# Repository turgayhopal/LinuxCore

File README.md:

# Linux-Core Development Board

- This project goal is developing myself about embedded linux environment like buildroot, the yacto project.

### Linux Core v2 Features

- NUC980 Series Microprocessor
- 2A Step-Down Voltage Regulator 1.2V, 1.8V, 3.3V
- RLT8188EU WIFI USB Module
- CP2102 USB TTL
- ILI9143 TFT LCD Header
- NAU88C22YG Audio Speaker
- Cam Slot
- SPI Nand External Flash
- MDBT5DQ (NRF52840 Bluetooth Bodule with USB) (Experimental !!!)
- 2 USB Host Socket
- 2 - 2x10 User Pin Header
- SD Card Slot
- 4 User LED's

### PCB Features

- 60.1mm x 80.1mm
- 1mm board thickness.
- 4 layer PCB.
- 0.45 / 0.3 vias

### Linux Core v1 Features

- NUC980 Series Microprocessor
- 2A Step-Down Voltage Regulator 1.2V, 1.8V, 3.3V
- RLT8188EU WIFI USB Module
- CP2102 USB TTL
- 128 KB External SPI-NOR Flash
- SD Card Slot
- 3 User LED's

### PCB Features

- 52.6mm x 57.5mm
- 1.6mm board thickness.
- 2 layer PCB.
- 0.6 / 0.3 vias

## Linux Core v2 Images

### Right Side

### Front Side

### Back Side

### LCD

## Linux Core v1 Images

### Right Side

### Front Side

### Back Side

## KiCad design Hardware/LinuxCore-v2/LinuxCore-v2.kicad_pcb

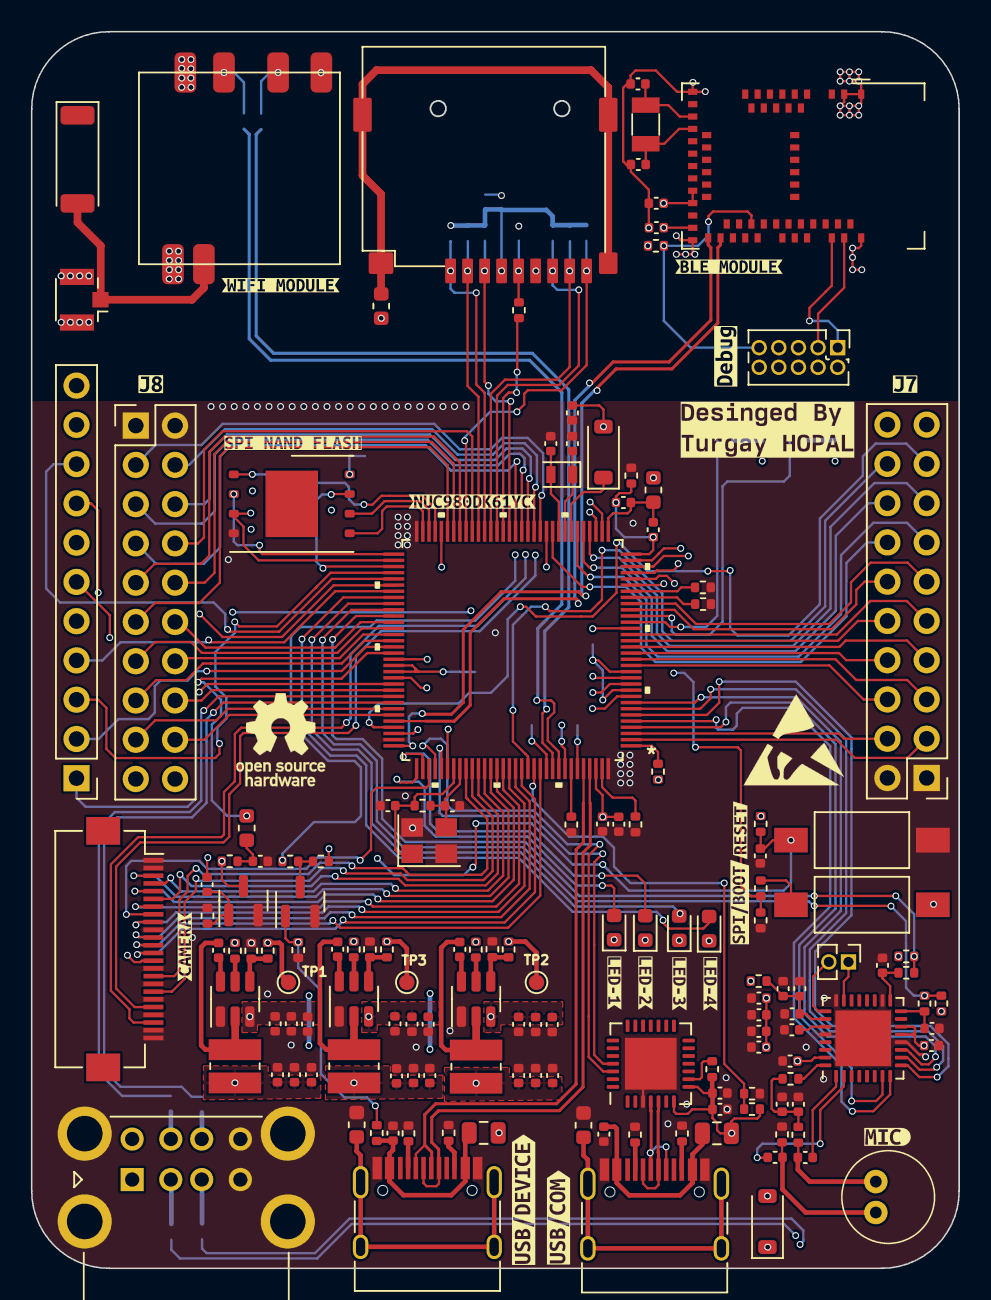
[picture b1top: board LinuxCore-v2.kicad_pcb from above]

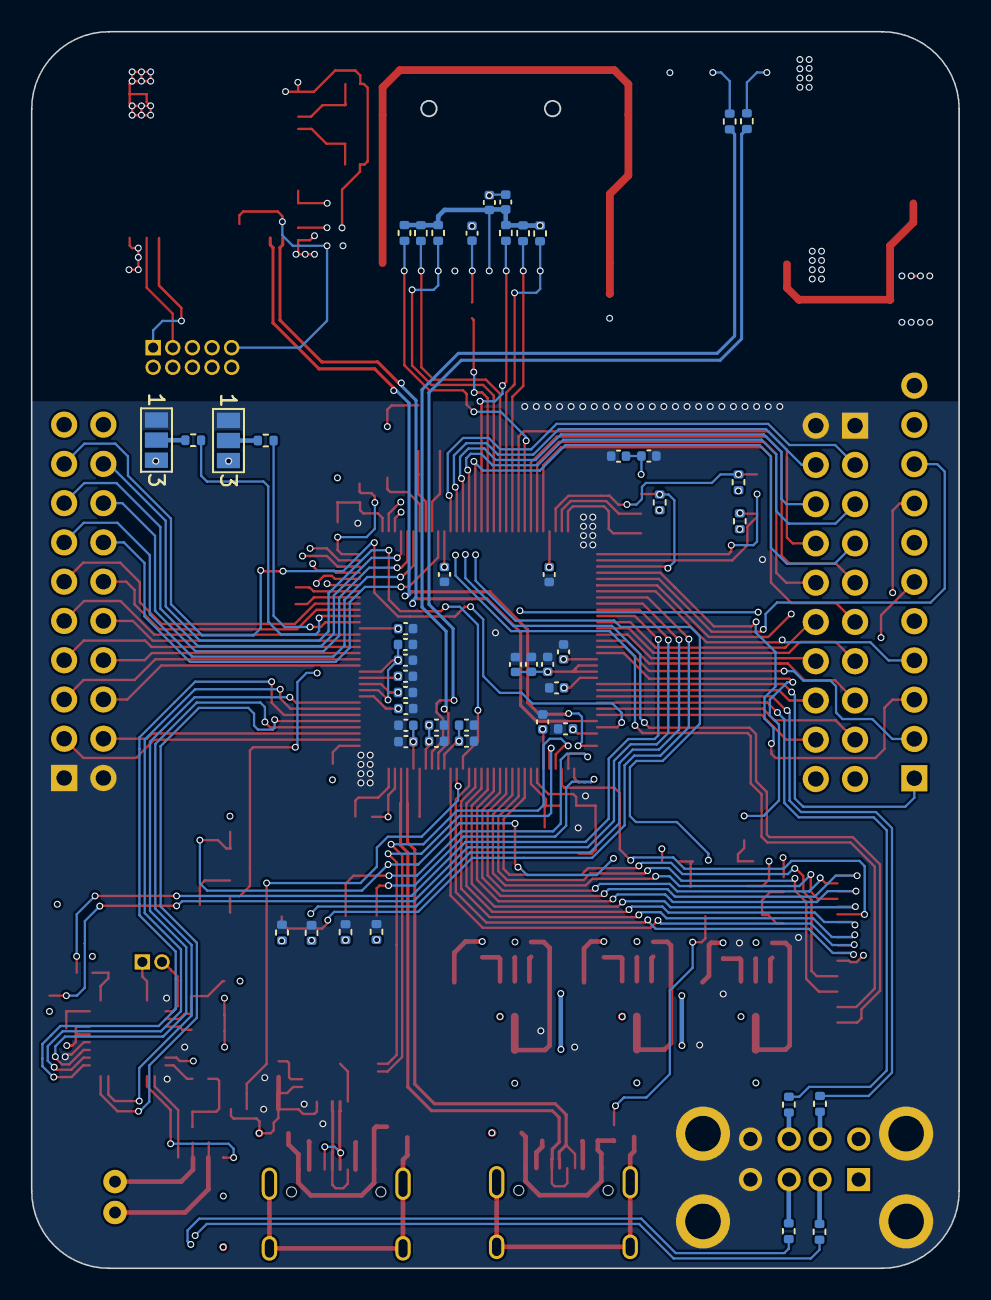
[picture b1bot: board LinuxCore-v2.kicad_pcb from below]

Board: 4 copper layers, 60.0 x 80.0 mm, 214 parts (49 on the bottom side), 174 nets.

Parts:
AE1: Antenna_Shield; U.FL_Hirose_U.FL-R-SMT-1_Vertical
AE2: Antenna_Shield; Johanson_2450AT43F0100
C1, C2, C3, C8: 15pF; C_0402_1005Metric
C4, C5, C6, C12, C33, C34, C38, C39, C40, C41, C42, C43, C61, C65, C66, C67, C69, C72, C78: 10uF; C_0402_1005Metric
C7, C9, C10, C11, C13, C17, C18, C19, C20, C21, C22, C23, C24, C25, C26, C27, C29, C30, C31, C32, C36, C37, C44, C45, C46, C47, C48, C49, C50, C51, C52, C60: 0.1uF; C_0402_1005Metric
C14, C15, C16, C28, C35, C53, C54, C55, C56, C57, C58, C70, C71: 1uF; C_0402_1005Metric
C59: NC; C_0402_1005Metric
C62, C63, C64, C68, C73, C74, C75, C77, C79: 100nF; C_0402_1005Metric
C76, C82, C83: 4.7uF; C_0402_1005Metric
C80, C81: 12pF; C_0402_1005Metric
D1: 30V 200mA; D_SOD-123
D2: B240; D_SOD-123
D3, D4, D5, D6: LED; LED_0603_1608Metric
F1, F2: 6V/1.5A; Fuse_0805_2012Metric
J1, J2: USB_C_Receptacle_USB2.0; USB_C_Receptacle_HRO_TYPE-C-31-M-12
J3: Conn_01x11_Pin; PinHeader_1x11_P2.54mm_Vertical
J4: Conn_01x24; Hirose_FH12-24S-0.5SH_1x24-1MP_P0.50mm_Horizontal
J5: NRF_Debug; PinHeader_2x05_P1.27mm_Vertical
J6: USB_A_Stacked; USB_A_CUI_UJ2-ADH-TH_Horizontal_Stacked
J7, J8: Conn_02x10_Odd_Even; PinHeader_2x10_P2.54mm_Vertical
JP1, JP2: SolderJumper_3_Open; SolderJumper-3_P1.3mm_Open_Pad1.0x1.5mm_NumberLabels
L1, L2, L3, L4, L8: 220R; L_0603_1608Metric
L5, L6, L7: 2.2uH; L_Wuerth_MAPI-3020
LS1: Speaker; PinHeader_1x02_P1.27mm_Vertical
Q1, Q2: MMBT3904; SOT-23
R1: 1M; R_0402_1005Metric
R2, R37, R48: 0R; R_0402_1005Metric
R3, R4, R12: 100K; R_0402_1005Metric
R5: 470R; R_0402_1005Metric
R6, R21, R23, R60, R61, R62, R63: 1K; R_0402_1005Metric
R7, R8, R25, R26, R56, R57, R58, R59: 5.1K; R_0402_1005Metric
R9: 20K; R_0402_1005Metric
R10: 39K; R_0402_1005Metric
R11, R13: 12.1K; R_0402_1005Metric
R14, R15: 4.7R; R_0402_1005Metric
R16, R17, R18, R19, R20, R22, R24, R27, R28, R29, R30, R31, R32, R33, R38, R39, R40, R41, R42, R43, R52, R53, R54, R55: 10K; R_0402_1005Metric
R34: 33.2K; R_0402_1005Metric
R35: 5.76K; R_0402_1005Metric
R36: 13.7K; R_0402_1005Metric
R44, R45, R46, R47: 33R; R_0402_1005Metric
R49, R50: 2.2K; R_0402_1005Metric
R51: 680R; R_0402_1005Metric
SW1, SW2: SW_Push; SW_SPST_FSMSM
TP1, TP2, TP3: TestPoint; TestPoint_Pad_D1.0mm
U1: NUC980DK61YC
U2: RLT8188_WIFI_MODUL
U3: CP2102N-Axx-xQFN28; QFN-28-1EP_5x5mm_P0.5mm_EP3.35x3.35mm
U4, U5, U6: TPS562200; SOT-23-6
U7: L-KLS1-TF-003; L-KLS1-TF-003-H1.85-R
U8: NAU88C22; QFN-32-1EP_5x5mm_P0.5mm_EP3.6x3.6mm
U9: F35SQA001G
U10: MDBT50Q-P1MV2; Raytac_MDBT50Q
U11: L-KLS3-MM6027PP-443
Y1: Crystal; Crystal_SMD_2012-2Pin_2.0x1.2mm
Y2: Crystal_GND24; Crystal_SMD_3225-4Pin_3.2x2.5mm
Y3: 32.768kHz; Crystal_SMD_3215-2Pin_3.2x1.5mm
kibuzzard-665B7D91: G***; kibuzzard-665B7D91
kibuzzard-665B7DAC: G***; kibuzzard-665B7DAC
kibuzzard-665B7DDA: G***; kibuzzard-665B7DDA
kibuzzard-665B7E6F: G***; kibuzzard-665B7E6F
kibuzzard-665B7E8B: G***; kibuzzard-665B7E8B
kibuzzard-665B7E24: G***; kibuzzard-665B7E24
kibuzzard-665B7E38: G***; kibuzzard-665B7E38
kibuzzard-665B7E84: G***; kibuzzard-665B7E84
kibuzzard-665B7E87: G***; kibuzzard-665B7E87
kibuzzard-665B7EA2: G***; kibuzzard-665B7EA2
kibuzzard-665B7EF0: G***; kibuzzard-665B7EF0
kibuzzard-665B7F01: G***; kibuzzard-665B7F01
kibuzzard-665B7F18: G***; kibuzzard-665B7F18
kibuzzard-665B7F32: G***; kibuzzard-665B7F32
kibuzzard-665B7FB9: G***; kibuzzard-665B7FB9
kibuzzard-665B7FBD: G***; kibuzzard-665B7FBD
kibuzzard-665C90BB: G***; kibuzzard-665C90BB
kibuzzard-665C92C9: G***; kibuzzard-665C92C9

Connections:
+1V2: C6.2, C11.2, C14.1, C17.2, C19.2, C22.2, C25.2, C29.2, C32.2, C34.2, C52.2, C55.2, C58.2, L7.2, R35.2, TP2.1, U1.10 (VDD), U1.13 (VDD), U1.43 (VDD), U1.82 (VDD), U1.94 (VDD), U1.118 (VDD), U1.123 (USB0_VDD)
+1V8: C20.1, C23.1, C26.1, C30.1, C33.1, C51.2, C54.2, C57.2, L6.2, R36.2, TP3.1, U1.11 (MVDD), U1.12 (MVDD), U1.83 (MVDD), U1.84 (MVDD)
+3V3: C4.2, C5.2, C7.2, C9.2, C10.2, C18.1, C21.1, C24.1, C27.1, C31.1, C50.2, C53.2, C56.2, C60.1, C61.1, C62.1, C63.1, C64.1, C66.1, C74.1, C75.2, C78.2, C79.2, C83.2, D1.2 (A), J3.5, J3.7, J3.10, J4.14, J5.2, J7.19, J7.20, J8.19, J8.20, JP1.3 (B), JP2.3 (B), L1.1, L5.2, R4.1, R12.1, R19.1, R34.2, R38.2, R39.2, R40.2, R41.2, R42.2, R43.2, R44.2, R45.2, R48.1, R52.1, R53.2, R54.1, R55.2, SW2.1, TP1.1, U1.9 (VDDIO), U1.20 (VDDIO), U1.60 (VDDIO), U1.85 (VDDIO), U1.102 (VDDIO), U1.121 (USB1_VDD33), U1.126 (USB0_VDD33), U2.1 (3V3), U7.4 (VDD), U8.13 (VDDC), U8.14 (VDDB), U8.31 (VDDA), U9.8 (VCC), U10.28 (VDD), U10.30 (VDDH)
/AUDIO/I2S_BCLK: U1.5 (PA-3), U8.8 (BCLK)
/AUDIO/I2S_DI: U1.6 (PA-4), U8.9 (ADCOUT)
/AUDIO/I2S_DO: U1.7 (PA-5), U8.10 (DACIN)
/AUDIO/I2S_LRCK: U1.4 (PA-2), U8.7 (FS)
/AUDIO/I2S_MCLK: U1.8 (PA-6), U8.11 (MCLK)
/AUDIO/LMICN: C71.2, U8.2 (LMICN)
/AUDIO/LMICP: C70.2, U8.1 (LMICP)
/AUDIO/LSPKOUT: LS1.2, U8.25 (LSPKOUT)
/AUDIO/RSPKOUT: LS1.1, U8.23 (RSPKOUT)
/AUDIO/SCL: R45.1, R47.1, U1.74 (PD-14)
/AUDIO/SCL_: C67.1, R47.2, U8.16 (SCLK)
/AUDIO/SDA: R44.1, R46.1, U1.75 (PD-15)
/AUDIO/SDA_: C65.1, R46.2, U8.17 (SDIO)
/AUDIO/SPK_3V3: C68.1, C69.1, C77.2, R48.2, U8.26 (VDDSPK)
/AUDIO/VREF: C76.2, U8.27 (VREF)
/BLE Module/NRESET: J5.9, R55.1, U10.40 (~RESET/P0.18)
/BLE Module/SWDCLK: J5.3, U10.53 (SWDCLK)
/BLE Module/SWDIO: J5.1, U10.51 (SWDIO)
/BLE Module/USB_D+: U1.96 (PF-7), U10.35 (D+)
/BLE Module/USB_D-: U1.92 (PF-6), U10.34 (D-)
/BLE Module/XL1: C80.1, U10.17 (XL1/P0.00), Y3.1
/BLE Module/XL2: C81.1, U10.18 (XL2/P0.01), Y3.2
/Deneyap Kamera/CAMD2: J4.6, U1.107 (PE-2)
/Deneyap Kamera/CAMD3: J4.4, U1.108 (PE-3)
/Deneyap Kamera/CAMD4: J4.3, U1.109 (PE-4)
/Deneyap Kamera/CAMD5: J4.5, U1.110 (PE-5)
/Deneyap Kamera/CAMD6: J4.7, U1.111 (PE-6)
/Deneyap Kamera/CAMD7: J4.9, U1.112 (PE-7)
/Deneyap Kamera/CAMD8: J4.11, U1.113 (PE-8)
/Deneyap Kamera/CAMD9: J4.13, U1.114 (PE-9)
/Deneyap Kamera/CAMH: J4.16, U1.105 (PE-0)
/Deneyap Kamera/CAMPC: J4.8, U1.99 (PF-10)
/Deneyap Kamera/CAMSC: J4.20, U1.35 (PB-5)
/Deneyap Kamera/CAMSD: J4.22, U1.34 (PB-7)
/Deneyap Kamera/CAMV: J4.18, U1.106 (PE-1)
/Deneyap Kamera/CAMXC: J4.12, U1.117 (PE-12)
/Header1/3: J7.3, U1.2 (PA-0)
/Header1/4: J7.4, U1.3 (PA-1)
/Header1/5: J7.5, U1.15 (PA-8)
/Header1/6: J7.6, U1.14 (PA-7)
/Header1/7: J7.7, U1.17 (PA-10)
/Header1/8: J7.8, U1.16 (PA-9)
/Header1/9: J7.9, U1.19 (PA-12)
/Header1/10: J7.10, U1.18 (PA-11)
/Header1/11: J7.11, U1.24 (PG-6)
/Header1/12: J7.12, U1.23 (PG-7)
/Header1/13: J7.13, U1.38 (PB-2)
/Header1/14: J7.14, U1.42 (PB-8)
/Header1/15: J7.15, U1.36 (PB-1)
/Header1/16: J7.16, U1.37 (PB-3)
/Header1/17: J7.17, U1.93 (PB-13)
/Header1/18: J7.18, U1.115 (PE-10)
/Header2/3: J8.3, U1.44 (PC-0)
/Header2/4: J8.4, U1.45 (PC-1)
/Header2/5: J8.5, U1.47 (PC-3)
/Header2/6: J8.6, U1.46 (PC-2)
/Header2/7: J8.7, U1.48 (PC-4)
/Header2/8: J8.8, U1.55 (PC-11)
/Header2/9: J8.9, U1.57 (PC-13)
/Header2/10: J8.10, U1.58 (PC-14)
/Header2/11: J8.11, U1.59 (PC-15)
/Header2/12: J8.12, U1.76 (PG-11)
/Header2/13: J8.13, U1.77 (PG-12)
/Header2/14: J8.14, U1.78 (PG-13)
/Header2/15: J8.15, U1.79 (PG-14)
/Header2/16: J8.16, U1.87 (PF-1)
/Header2/17: J8.17, U1.90 (PF-4)
/Header2/18: J8.18, U1.91 (PF-5)
/ILI9143 TFT LCD/CLK: J3.9, U1.69 (PD-9)
/ILI9143 TFT LCD/CS1: J3.3, U1.68 (PD-8)
/ILI9143 TFT LCD/CS2: J3.2, U1.80 (PG-15)
/ILI9143 TFT LCD/DC: J3.6, U1.29 (PB-0)
/ILI9143 TFT LCD/MISO: J3.4, U1.71 (PD-11)
/ILI9143 TFT LCD/MOSI: J3.8, U1.70 (PD-10)
/ILI9143 TFT LCD/PEN: J3.1, U1.86 (PF-0)
/MPU/PB4: R56.2, U1.31 (PB-4)
/MPU/PB6: R57.2, U1.30 (PB-6)
/MPU/PC5: R42.1, U1.49 (PC-5), U7.3 (CMD)
/MPU/PC6: R37.2, U1.50 (PC-6)
/MPU/PC7: R43.1, U1.51 (PC-7), U7.7 (DAT0)
/MPU/PC8: R41.1, U1.52 (PC-8), U7.8 (DAT1)
/MPU/PC9: R38.1, U1.53 (PC-9), U7.1 (DAT2)
/MPU/PC10: R40.1, U1.54 (PC-10), U7.2 (CD/DAT3)
/MPU/PC12: R39.1, U1.56 (PC-12), U7.9 (CD)
/MPU/PD2: R53.1, U1.61 (PD-2), U9.1 (CS#)
/MPU/PD3: U1.62 (PD-3), U9.6 (CLK)
/MPU/PD4: U1.63 (PD-4), U9.5 (DI/SIO0)
/MPU/PD5: U1.65 (PD-5), U9.2 (DO/SIO1)
/MPU/PD6: R52.2, U1.66 (PD-6), U9.3 (WP#/SIO2)
/MPU/PD7: R54.2, U1.67 (PD-7), U9.7 (HOLD#/SIO3)
/MPU/PD12: D5.2 (A), U1.72 (PD-12)
/MPU/PD13: D6.2 (A), U1.73 (PD-13)
/MPU/PE11: R9.1, R10.2, U1.116 (PE-11)
/MPU/PF2: R59.2, U1.88 (PF-2)
/MPU/PF3: R58.2, U1.89 (PF-3)
/MPU/PF8: D3.2 (A), U1.97 (PF-8)
/MPU/PF9: D4.2 (A), U1.98 (PF-9)
/MPU/PF11: U1.100 (PF-11), U3.26 (TXD)
/MPU/PF12: U1.101 (PF-12), U3.25 (RXD)
/MPU/PG0: R21.1, U1.28 (PG-0)
/MPU/PG1: R23.1, R24.1, U1.27 (PG-1)
/MPU/PG3: R16.1, U1.26 (PG-3)
/MPU/PG5: R17.1, U1.25 (PG-5)
/MPU/PG8: R20.1, U1.22 (PG-8)
/MPU/PG9: R22.1, U1.21 (PG-9)
/MPU/USB0_D+: J1.A6 (D+), J1.B6 (D+), U1.125 (USB0_DP)
/MPU/USB0_D-: J1.A7 (D-), J1.B7 (D-), U1.124 (USB0_DM)
/MPU/USB0_ID: R12.2, U1.1 (USB0_ID)
/MPU/USB0_REXT: R11.2, U1.127 (USB0_REXT)
/MPU/USB1_D+: R15.2, U1.120 (USB1_DP)
/MPU/USB1_D-: R14.2, U1.119 (USB1_DM)
/MPU/USB1_REXT: R13.2, U1.122 (USB1_REXT)
/MPU/USB_DETECT: Q2.1 (B), R6.1, R18.1
/MPU/X32_IN: C1.1, U1.40 (X32_IN), Y1.1
/MPU/X32_OUT: C2.1, U1.41 (X32_OUT), Y1.2
/MPU/XT_IN: C3.1, R1.1, U1.103 (XT_IN), Y2.1
/MPU/XT_OUT: C8.1, R1.2, U1.104 (XT_OUT), Y2.3
/MPU/nRESET: C15.1, Q1.3 (C), R4.2, R5.2, SW1.2
/MPU/nRST: L2.2, U1.81 (nRESET)
/USB/USB_D+: J2.A6 (D+), J2.B6 (D+), U3.4 (D+)
/USB/USB_D-: J2.A7 (D-), J2.B7 (D-), U3.5 (D-)
/Voltage Supply/SW_1: C49.2, L7.1, U6.2 (SW)
/Voltage Supply/SW_2: C48.2, L6.1, U5.2 (SW)
/Voltage Supply/SW_3: C47.2, L5.1, U4.2 (SW)
/Voltage Supply/VBST_1: C49.1, U6.6 (VBST)
/Voltage Supply/VBST_2: C48.1, U5.6 (VBST)
/Voltage Supply/VBST_3: C47.1, U4.6 (VBST)
/Voltage Supply/VIN: C38.2, C39.2, C40.2, C41.2, C42.2, C43.2, C44.2, C45.2, C46.2, D2.1 (K), R28.2, R29.2, R30.2, U4.3 (VIN), U5.3 (VIN), U6.3 (VIN)
GND: AE1.2 (Shield), C1.2, C2.2, C3.2, C4.1, C5.1, C6.1, C7.1, C8.2, C9.1, C10.1, C11.1, C15.2, C16.1, C17.1, C18.2, C19.1, C20.2, C21.2, C22.1, C23.2, C24.2, C25.1, C26.2, C27.2, C28.1, C29.1, C30.2, C31.2, C32.1, C33.2, C34.1, C35.1, C36.1, C37.2, C38.1, C39.1, C40.1, C41.1, C42.1, C43.1, C44.1, C45.1, C46.1, C50.1, C51.1, C52.1, C53.1, C54.1, C55.1, C56.1, C57.1, C58.1, C59.2, C60.2, C61.2, C62.2, C63.2, C64.2, C65.2, C66.2, C67.2, C68.2, C69.2, C72.2, C73.2, C74.2, C75.1, C76.1, C77.1, C78.1, C79.1, C80.2, C81.2, C82.1, C83.1, J1.A1 (GND), J1.A12 (GND), J1.B1 (GND), J1.B12 (GND), J2.A1 (GND), J2.A12 (GND), J2.B1 (GND), J2.B12 (GND), J3.11, J4.1, J4.2, J4.10, J4.15, J4.17, J4.19, J4.21, J4.23, J4.24, J5.4, J5.6, J6.4 (GND1), J6.8 (GND2), J6.9 (Shield), J7.1, J7.2, J8.1, J8.2, JP1.1 (A), JP2.1 (A), L3.2, L4.2, L8.2, Q1.2 (E), Q2.2 (E), R2.1, R3.2, R7.2, R8.2, R10.1, R11.1, R13.1, R16.2, R17.2, R18.2, R24.2, R25.2, R26.2, R31.1, R32.1, R33.1, R50.2, R60.2, R61.2, R62.2, R63.2, SW1.1, U1.64 (VSS), U1.95 (PLL_VSS), U1.128 (VSS), U2.4 (VSS), U2.5 (VSS), U3.3 (GND), U3.29 (GND), U4.1 (GND), U5.1 (GND), U6.1 (GND), U7.6 (VSS), U8.12 (VSSD), U8.18 (MODE), U8.24 (VSSSPK), U8.28 (VSSA), U8.33 (EPAD), U9.4 (GND), U10.1 (GND), U10.2 (GND), U10.15 (GND), U10.33 (GND), U10.55 (GND), Y2.2, Y2.4
unnamed: AE1.1 (A), AE2.2 (Shield), U2.6 (ANT)
unnamed: C16.2, L2.1, R5.1
unnamed: C28.2, F1.1, J1.A4 (VBUS), J1.A9 (VBUS), J1.B4 (VBUS), J1.B9 (VBUS), R6.2
unnamed: C35.2, F2.1, J2.A4 (VBUS), J2.A9 (VBUS), J2.B4 (VBUS), J2.B9 (VBUS)
unnamed: C70.1, R49.2, U11.1
unnamed: C71.1, R50.1, U11.2
unnamed: C72.1, C73.1, R49.1, R51.2
unnamed: D1.1 (K), U1.39 (VBAT33)
unnamed: D3.1 (K), R61.1
unnamed: D4.1 (K), R62.1
unnamed: D5.1 (K), R63.1
unnamed: D6.1 (K), R60.1
unnamed: J1.A5 (CC1), R7.1
unnamed: J1.B5 (CC2), R8.1
unnamed: J1.S1 (SHIELD), L3.1
unnamed: J2.A5 (CC1), R25.1
unnamed: J2.B5 (CC2), R26.1
unnamed: J2.S1 (SHIELD), L4.1
unnamed: J6.3 (D1+), R56.1
unnamed: J6.2 (D1-), R57.1
unnamed: J6.7 (D2+), R58.1
unnamed: J6.6 (D2-), R59.1
unnamed: JP1.2 (C), R20.2
unnamed: JP2.2 (C), R22.2
unnamed: L8.1, U7.10 (SHIELD), U7.11 (SHIELD), U7.12 (SHIELD), U7.13 (SHIELD)
unnamed: C14.2, Q1.1 (B), R3.1
unnamed: Q2.3 (C), R19.2, R21.2
unnamed: R23.2, SW2.2
unnamed: C12.1, C13.1, L1.2, U1.33 (AVDDADC)
unnamed: C12.2, C13.2, R2.2, U1.32 (AVSSADC)
unnamed: R14.1, U2.2 (USB_DM)
unnamed: R15.1, U2.3 (USB_DP)
unnamed: R27.2, U3.9 (~RST)
unnamed: R28.1, U4.5 (EN)
unnamed: R31.2, R34.1, U4.4 (VFB)
unnamed: R29.1, U5.5 (EN)
unnamed: R32.2, R36.1, U5.4 (VFB)
unnamed: R30.1, U6.5 (EN)
unnamed: R33.2, R35.1, U6.4 (VFB)
unnamed: C59.1, R37.1, U7.5 (CLK)
unnamed: R51.1, U8.32 (MICBIAS)
VBUS: C36.2, C37.1, C82.2, D2.2 (A), F1.2, F2.2, J6.1 (VBUS1), J6.5 (VBUS2), R9.2, R27.1, U3.7 (VREGIN), U3.8 (VBUS), U10.32 (VBUS)

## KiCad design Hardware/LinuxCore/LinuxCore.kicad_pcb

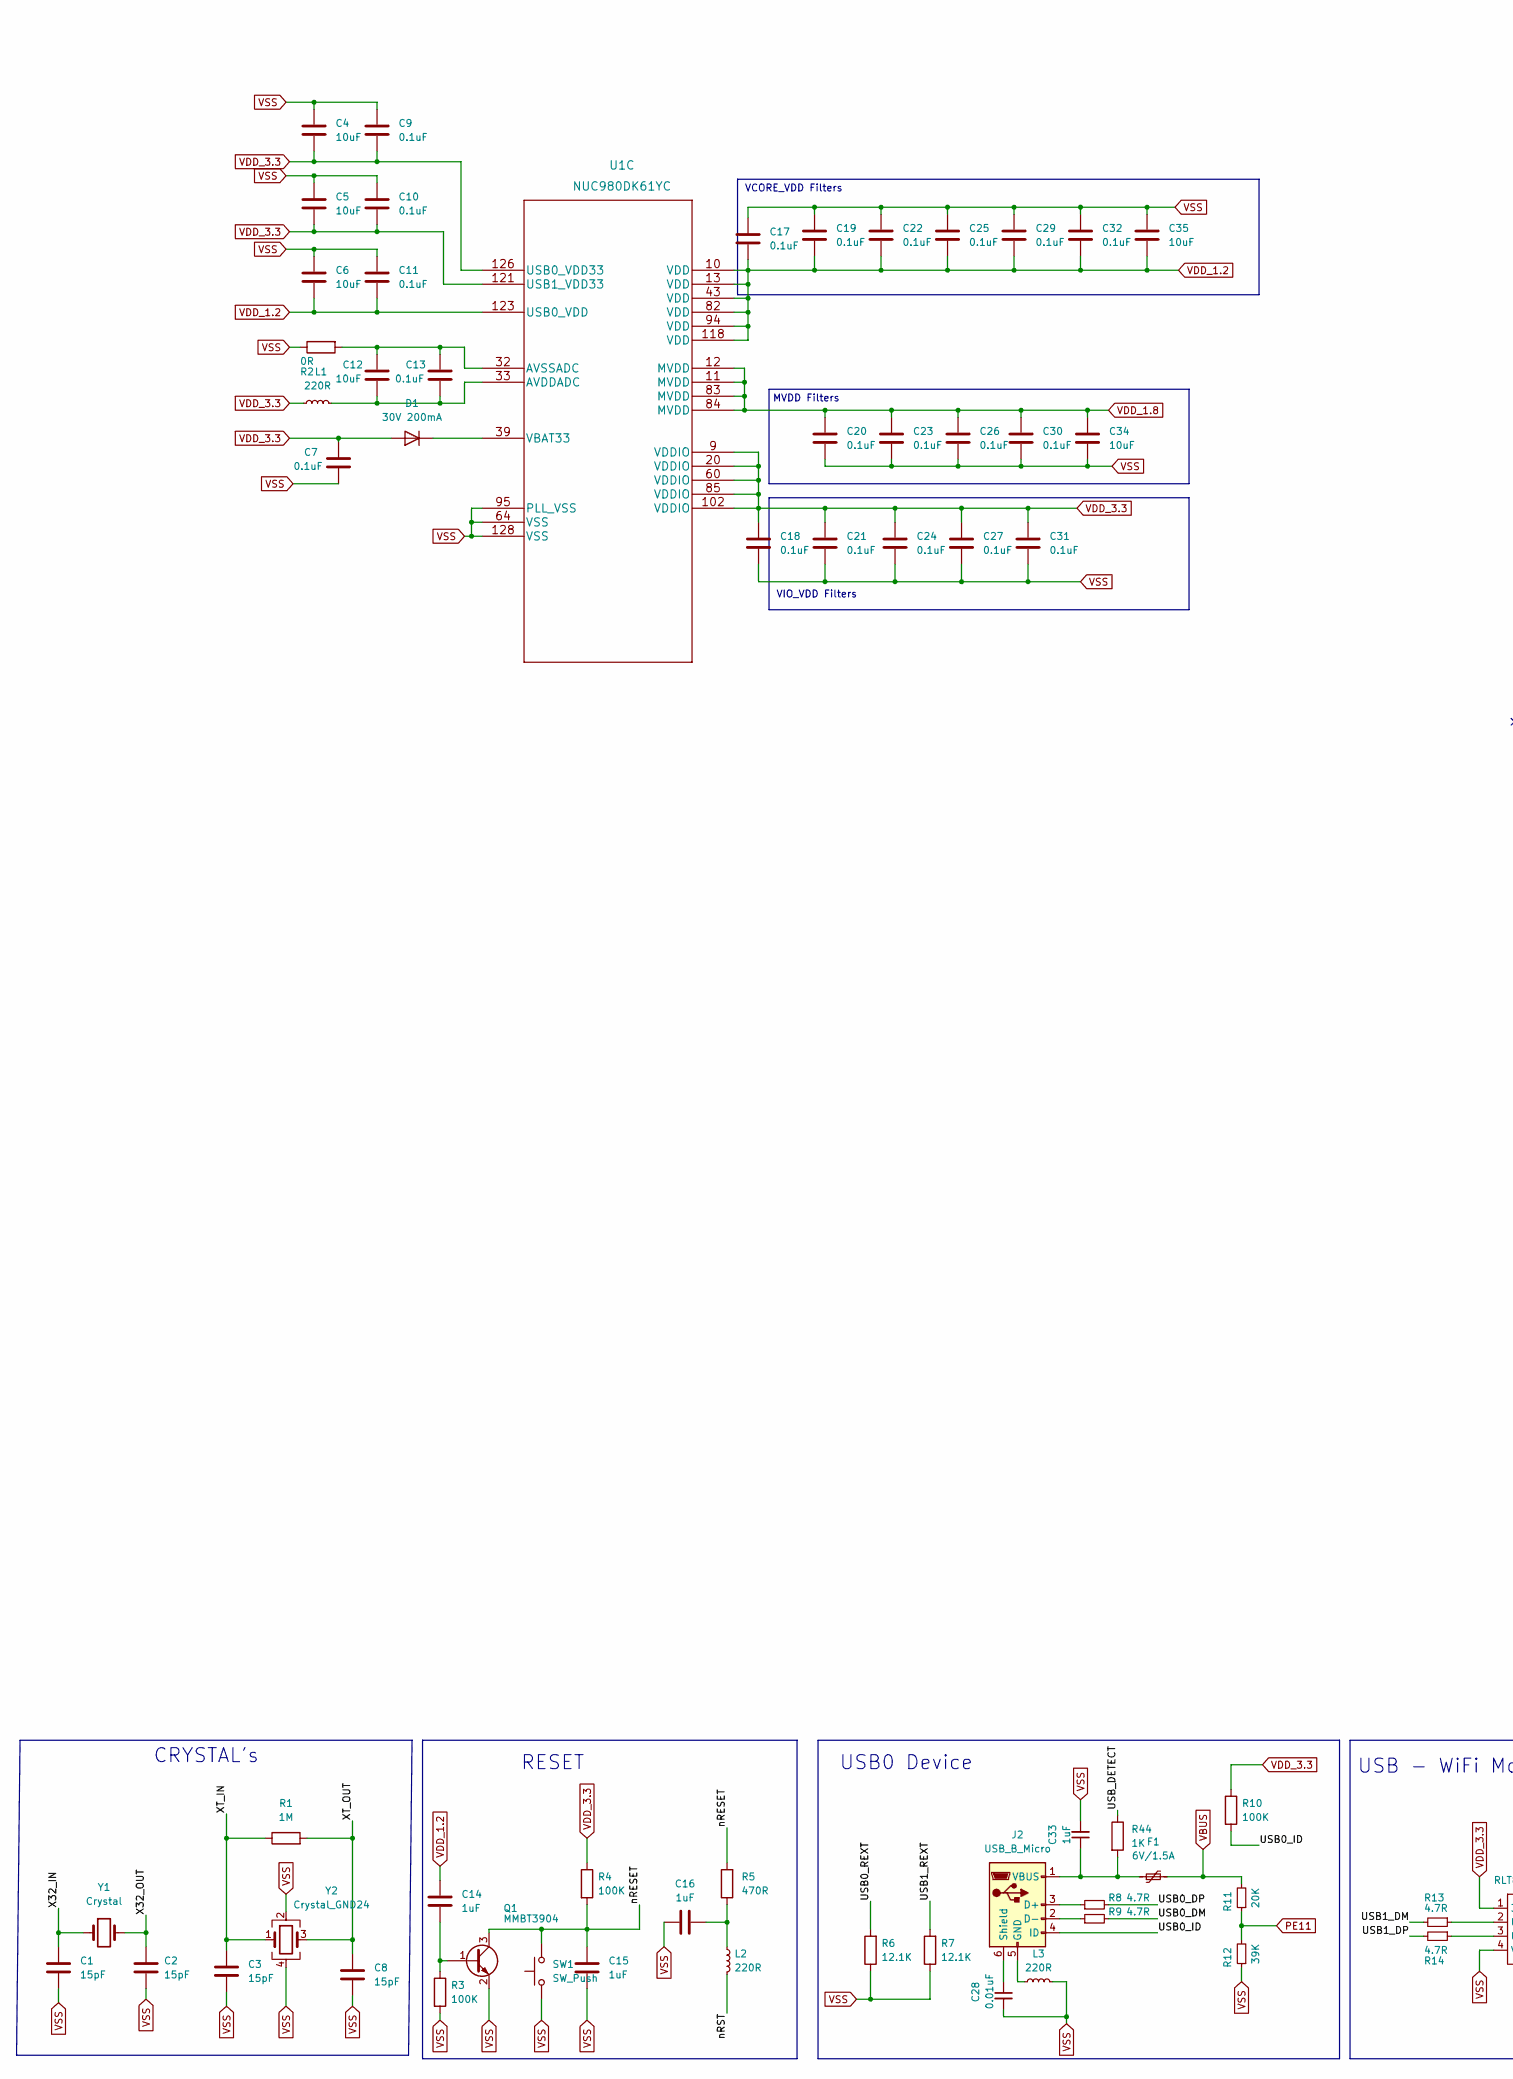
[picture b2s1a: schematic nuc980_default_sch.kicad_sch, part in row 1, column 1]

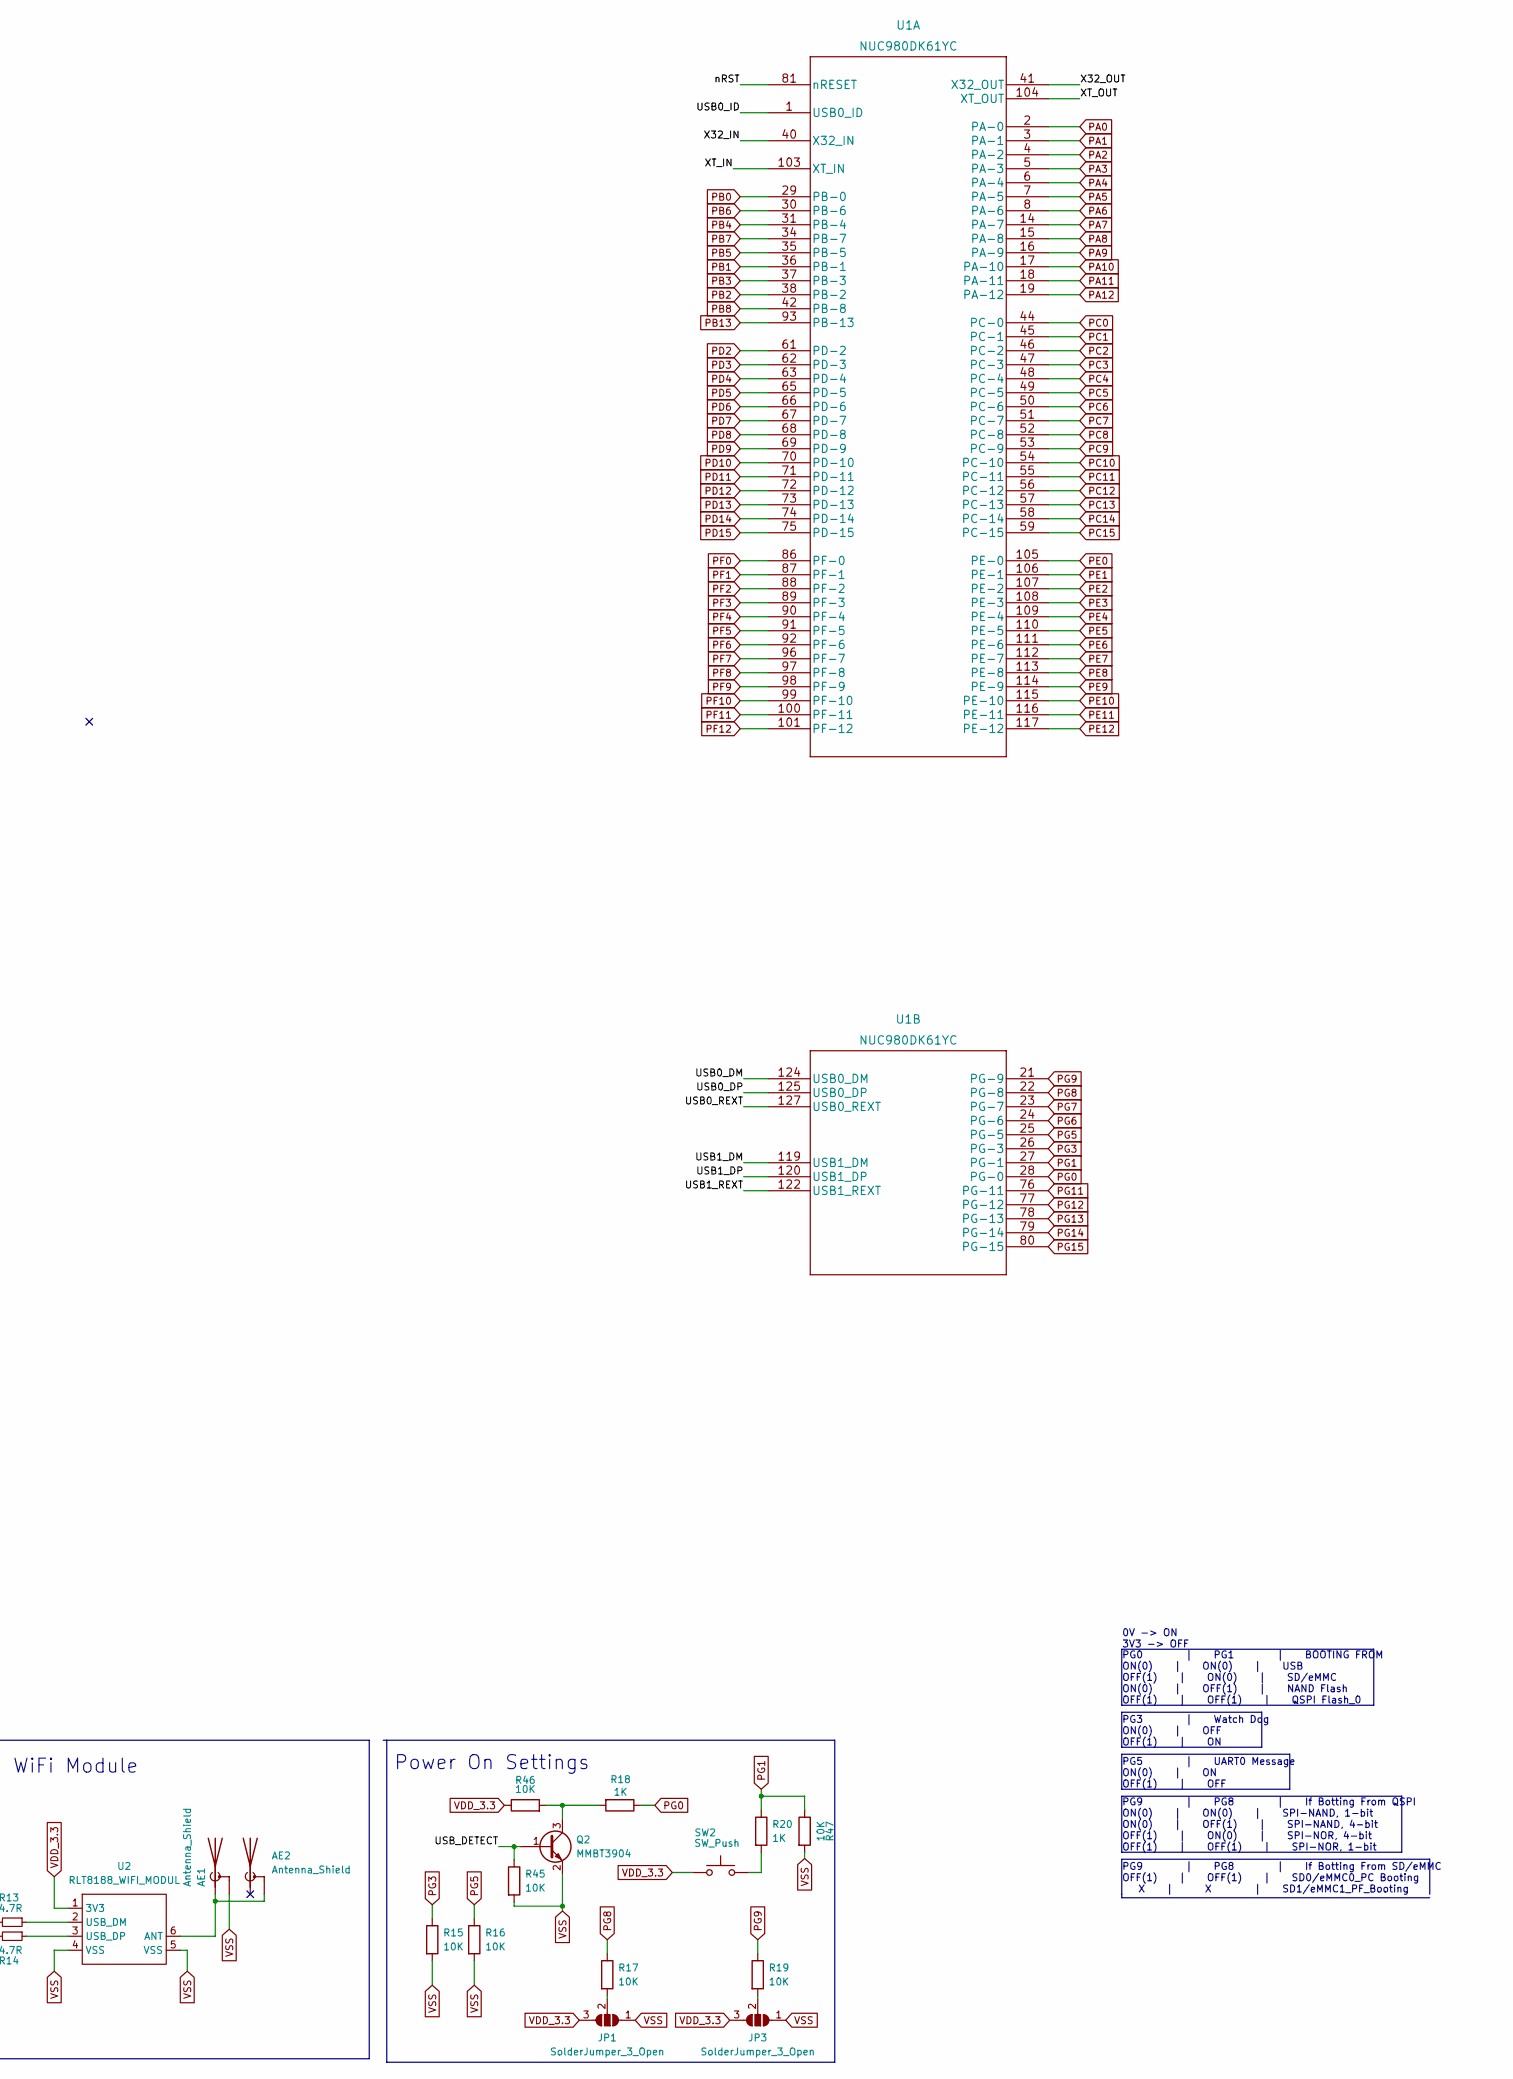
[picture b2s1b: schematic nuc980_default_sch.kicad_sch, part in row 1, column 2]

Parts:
AE1: Antenna_Shield; U.FL_Hirose_U.FL-R-SMT-1_Vertical
AE2: Antenna_Shield; Johanson_2450AT43F0100
C1, C2, C3, C8: 15pF; C_0402_1005Metric
C4, C5, C6, C12, C34, C35: 10uF; C_0402_1005Metric
C7, C9, C10, C11, C13, C17, C18, C19, C20, C21, C22, C23, C24, C25, C26, C27, C29, C30, C31, C32: 0.1uF; C_0402_1005Metric
C14, C15, C16, C33: 1uF; C_0402_1005Metric
C28: 0.01uF; C_0402_1005Metric
D1: 30V 200mA; D_SOD-123
F1: 6V/1.5A; Fuse_0805_2012Metric
J2: USB_B_Micro; USB_Micro-B_Amphenol_10118194_Horizontal
JP1, JP3: SolderJumper_3_Open; SolderJumper-3_P1.3mm_Open_Pad1.0x1.5mm_NumberLabels
L1, L2, L3: 220R; L_0603_1608Metric
Q1, Q2: MMBT3904; SOT-23
R1: 1M; R_0402_1005Metric
R2: 0R; R_0402_1005Metric
R3, R4, R10: 100K; R_0402_1005Metric
R5: 470R; R_0402_1005Metric
R6, R7: 12.1K; R_0402_1005Metric
R8, R9, R13, R14: 4.7R; R_0402_1005Metric
R11: 20K; R_0402_1005Metric
R12: 39K; R_0402_1005Metric
R15, R16, R17, R19, R45, R46, R47: 10K; R_0402_1005Metric
R18, R20, R44: 1K; R_0402_1005Metric
SW1, SW2: SW_Push; SW_SPST_FSMSM
U1: NUC980DK61YC
U2: RLT8188_WIFI_MODUL
Y1: Crystal; Crystal_SMD_2012-2Pin_2.0x1.2mm
Y2: Crystal_GND24; Crystal_SMD_3225-4Pin_3.2x2.5mm

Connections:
/NUC980/USB0_DM: R9.2, U1.124 (USB0_DM)
/NUC980/USB0_DP: R8.2, U1.125 (USB0_DP)
/NUC980/USB0_ID: J2.4 (ID), R10.2, U1.1 (USB0_ID)
/NUC980/USB0_REXT: R6.2, U1.127 (USB0_REXT)
/NUC980/USB1_DM: R13.2, U1.119 (USB1_DM)
/NUC980/USB1_DP: R14.2, U1.120 (USB1_DP)
/NUC980/USB1_REXT: R7.2, U1.122 (USB1_REXT)
/NUC980/USB_DETECT: Q2.1 (B), R44.1, R45.1
/NUC980/X32_IN: C1.1, U1.40 (X32_IN), Y1.1
/NUC980/X32_OUT: C2.1, U1.41 (X32_OUT), Y1.2
/NUC980/XT_IN: C3.1, R1.1, U1.103 (XT_IN), Y2.1
/NUC980/XT_OUT: C8.1, R1.2, U1.104 (XT_OUT), Y2.3
/NUC980/nRESET: C15.1, Q1.3 (C), R4.2, R5.2, SW1.2
/NUC980/nRST: L2.2, U1.81 (nRESET)
unnamed: AE1.1 (A), AE2.2 (Shield), U2.6 (ANT)
unnamed: C12.1, C13.1, L1.2, U1.33 (AVDDADC)
unnamed: C12.2, C13.2, R2.2, U1.32 (AVSSADC)
unnamed: C14.2, Q1.1 (B), R3.1
unnamed: C16.2, L2.1, R5.1
unnamed: C28.1, J2.6 (Shield)
unnamed: C33.1, F1.1, J2.1 (VBUS), R44.2
unnamed: D1.1 (K), U1.39 (VBAT33)
unnamed: J2.2 (D-), R9.1
unnamed: J2.3 (D+), R8.1
unnamed: J2.5 (GND), L3.1
unnamed: JP1.2 (C), R17.2
unnamed: JP3.2 (C), R19.2
unnamed: R13.1, U2.2 (USB_DM)
unnamed: R14.1, U2.3 (USB_DP)
unnamed: Q2.3 (C), R18.2, R46.2
unnamed: R20.2, SW2.2
PA0: U1.2 (PA-0)
PA1: U1.3 (PA-1)
PA2: U1.4 (PA-2)
PA3: U1.5 (PA-3)
PA4: U1.6 (PA-4); also elsewhere on the board
PA5: U1.7 (PA-5); also elsewhere on the board
PA6: U1.8 (PA-6); also elsewhere on the board
PA7: U1.14 (PA-7)
PA8: U1.15 (PA-8)
PA9: U1.16 (PA-9)
PA10: U1.17 (PA-10)
PA11: U1.18 (PA-11)
PA12: U1.19 (PA-12)
PB0: U1.29 (PB-0); also elsewhere on the board
PB1: U1.36 (PB-1)
PB2: U1.38 (PB-2)
PB3: U1.37 (PB-3)
PB4: U1.31 (PB-4)
PB5: U1.35 (PB-5)
PB6: U1.30 (PB-6)
PB7: U1.34 (PB-7)
PB8: U1.42 (PB-8)
PB13: U1.93 (PB-13); also elsewhere on the board
PC0: U1.44 (PC-0)
PC1: U1.45 (PC-1)
PC2: U1.46 (PC-2)
PC3: U1.47 (PC-3)
PC4: U1.48 (PC-4)
PC5: U1.49 (PC-5); also elsewhere on the board
PC6: U1.50 (PC-6); also elsewhere on the board
PC7: U1.51 (PC-7); also elsewhere on the board
PC8: U1.52 (PC-8); also elsewhere on the board
PC9: U1.53 (PC-9); also elsewhere on the board
PC10: U1.54 (PC-10); also elsewhere on the board
PC11: U1.55 (PC-11)
PC12: U1.56 (PC-12); also elsewhere on the board
PC13: U1.57 (PC-13)
PC14: U1.58 (PC-14)
PC15: U1.59 (PC-15)
PD2: U1.61 (PD-2); also elsewhere on the board
PD3: U1.62 (PD-3); also elsewhere on the board
PD4: U1.63 (PD-4); also elsewhere on the board
PD5: U1.65 (PD-5); also elsewhere on the board
PD6: U1.66 (PD-6); also elsewhere on the board
PD7: U1.67 (PD-7); also elsewhere on the board
PD8: U1.68 (PD-8); also elsewhere on the board
PD9: U1.69 (PD-9); also elsewhere on the board
PD10: U1.70 (PD-10); also elsewhere on the board
PD11: U1.71 (PD-11); also elsewhere on the board
PD12: U1.72 (PD-12); also elsewhere on the board
PD13: U1.73 (PD-13); also elsewhere on the board
PD14: U1.74 (PD-14); also elsewhere on the board
PD15: U1.75 (PD-15); also elsewhere on the board
PE0: U1.105 (PE-0)
PE1: U1.106 (PE-1)
PE2: U1.107 (PE-2)
PE3: U1.108 (PE-3)
PE4: U1.109 (PE-4)
PE5: U1.110 (PE-5)
PE6: U1.111 (PE-6)
PE7: U1.112 (PE-7)
PE8: U1.113 (PE-8)
PE9: U1.114 (PE-9)
PE10: U1.115 (PE-10)
PE11: R11.1, R12.2, U1.116 (PE-11)
PE12: U1.117 (PE-12)
PF0: U1.86 (PF-0); also elsewhere on the board
PF1: U1.87 (PF-1); also elsewhere on the board
PF2: U1.88 (PF-2); also elsewhere on the board
PF3: U1.89 (PF-3); also elsewhere on the board
PF4: U1.90 (PF-4); also elsewhere on the board
PF5: U1.91 (PF-5); also elsewhere on the board
PF6: U1.92 (PF-6); also elsewhere on the board
PF7: U1.96 (PF-7); also elsewhere on the board
PF8: U1.97 (PF-8); also elsewhere on the board
PF9: U1.98 (PF-9); also elsewhere on the board
PF10: U1.99 (PF-10); also elsewhere on the board
PF11: U1.100 (PF-11); also elsewhere on the board
PF12: U1.101 (PF-12); also elsewhere on the board
PG0: R18.1, U1.28 (PG-0)
PG1: R20.1, R47.1, U1.27 (PG-1)
PG3: R15.1, U1.26 (PG-3)
PG5: R16.1, U1.25 (PG-5)
PG6: U1.24 (PG-6)
PG7: U1.23 (PG-7)
PG8: R17.1, U1.22 (PG-8)
PG9: R19.1, U1.21 (PG-9)
PG11: U1.76 (PG-11); also elsewhere on the board
PG12: U1.77 (PG-12); also elsewhere on the board
PG13: U1.78 (PG-13); also elsewhere on the board
PG14: U1.79 (PG-14); also elsewhere on the board
PG15: U1.80 (PG-15); also elsewhere on the board
VBUS: F1.2, R11.2; also elsewhere on the board
VDD_1.2: C6.2, C11.2, C14.1, C17.2, C19.2, C22.2, C25.2, C29.2, C32.2, C35.2, U1.10 (VDD), U1.13 (VDD), U1.43 (VDD), U1.82 (VDD), U1.94 (VDD), U1.118 (VDD), U1.123 (USB0_VDD); also elsewhere on the board
VDD_1.8: C20.1, C23.1, C26.1, C30.1, C34.1, U1.11 (MVDD), U1.12 (MVDD), U1.83 (MVDD), U1.84 (MVDD); also elsewhere on the board
VDD_3.3: C4.2, C5.2, C7.2, C9.2, C10.2, C18.1, C21.1, C24.1, C27.1, C31.1, D1.2 (A), JP1.3 (B), JP3.3 (B), L1.1, R4.1, R10.1, R46.1, SW2.1, U1.9 (VDDIO), U1.20 (VDDIO), U1.60 (VDDIO), U1.85 (VDDIO), U1.102 (VDDIO), U1.121 (USB1_VDD33), U1.126 (USB0_VDD33), U2.1 (3V3); also elsewhere on the board
VSS: AE1.2 (Shield), C1.2, C2.2, C3.2, C4.1, C5.1, C6.1, C7.1, C8.2, C9.1, C10.1, C11.1, C15.2, C16.1, C17.1, C18.2, C19.1, C20.2, C21.2, C22.1, C23.2, C24.2, C25.1, C26.2, C27.2, C28.2, C29.1, C30.2, C31.2, C32.1, C33.2, C34.2, C35.1, JP1.1 (A), JP3.1 (A), L3.2, Q1.2 (E), Q2.2 (E), R2.1, R3.2, R6.1, R7.1, R12.1, R15.2, R16.2, R45.2, R47.2, SW1.1, U1.64 (VSS), U1.95 (PLL_VSS), U1.128 (VSS), U2.4 (VSS), U2.5 (VSS), Y2.2, Y2.4; also elsewhere on the board

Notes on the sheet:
PG9 | PG8 | If Botting From SD/eMMC OFF(1) | OFF(1) | SD0/eMMC0_PC Booting X | X | SD1/eMMC1_PF_Booting
MVDD Filters
RESET
USB0 Device
VCORE_VDD Filters
USB - WiFi Module
PG0 | PG1 | BOOTING FROM ON(0) | ON(0) | USB OFF(1) | ON(0) | SD/eMMC ON(0) | OFF(1) | NAND Flash OFF(1) | OFF(1) | QSPI Flash_0
0V -> ON 3V3 -> OFF
PG9 | PG8 | If Botting From QSPI ON(0) | ON(0) | SPI-NAND, 1-bit ON(0) | OFF(1) | SPI-NAND, 4-bit OFF(1) | ON(0) | SPI-NOR, 4-bit OFF(1) | OFF(1) | SPI-NOR, 1-bit
PG5 | UART0 Message ON(0) | ON OFF(1) | OFF
CRYSTAL's
Power On Settings
VIO_VDD Filters
PG3 | Watch Dog ON(0) | OFF OFF(1) | ON

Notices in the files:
parts and their libraries:
Copyright 2021 Accelerated Designs. All rights reserved.
